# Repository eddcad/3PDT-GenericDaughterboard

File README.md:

# 3PDT-DBoard

Very basic 3PDT Daughterbard with no LED or CLR. There is a "No-Net" pour on the
board as there is no specific ground to refer to. This arises because the board
is intended to be used in conjuction with other boards I have developed that
include the full circuit with different pad I/O requirements.

This board is intended to negate the need to individually solder all of the
individual legs on the 3PDT to wires (I'm inheritantly lazy, life is too short
and I have a mind to waste.)

Having read this, do with it what you will!

Happy soldering.

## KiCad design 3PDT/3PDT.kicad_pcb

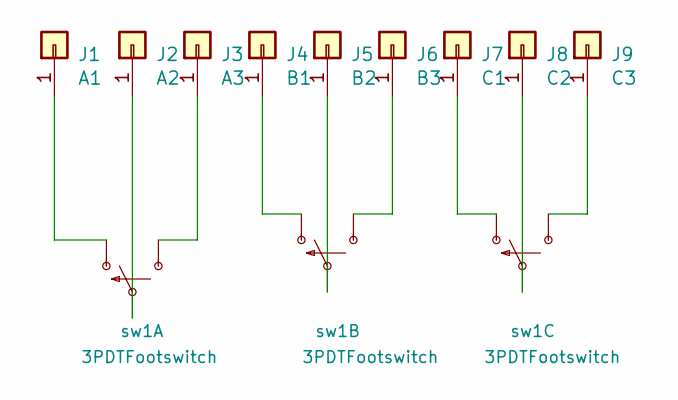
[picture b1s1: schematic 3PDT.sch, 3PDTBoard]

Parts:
J1: A1; SolderWire-0.25sqmm_1x01_D0.65mm_OD1.7mm
J2: A2; SolderWire-0.25sqmm_1x01_D0.65mm_OD1.7mm
J3: A3; SolderWire-0.25sqmm_1x01_D0.65mm_OD1.7mm
J4: B1; SolderWire-0.25sqmm_1x01_D0.65mm_OD1.7mm
J5: B2; SolderWire-0.25sqmm_1x01_D0.65mm_OD1.7mm
J6: B3; SolderWire-0.25sqmm_1x01_D0.65mm_OD1.7mm
J7: C1; SolderWire-0.25sqmm_1x01_D0.65mm_OD1.7mm
J8: C2; SolderWire-0.25sqmm_1x01_D0.65mm_OD1.7mm
J9: C3; SolderWire-0.25sqmm_1x01_D0.65mm_OD1.7mm
sw1: 3PDTFootswitch; STOMP_SWITCH_3PDT

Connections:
unnamed: J1.1, sw1.A1
unnamed: J2.1, sw1.A2
unnamed: J3.1, sw1.A3
unnamed: J4.1, sw1.B1
unnamed: J5.1, sw1.B2
unnamed: J6.1, sw1.B3
unnamed: J7.1, sw1.C1
unnamed: J8.1, sw1.C2
unnamed: J9.1, sw1.C3

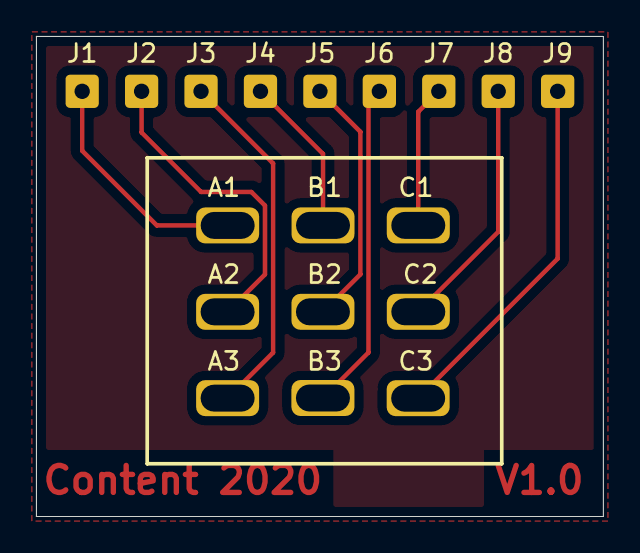
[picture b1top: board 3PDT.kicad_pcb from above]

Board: 2 copper layers, 31.5 x 26.7 mm, 10 parts (0 on the bottom side), 9 nets.

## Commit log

2020-09-28 Completed simple 3PDT board
2020-10-03 README scribbled upon
2020-10-03 Rewritten to actually make some sense
